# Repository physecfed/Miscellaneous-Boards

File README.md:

# Miscellaneous-Boards
A repository for miscellaneous KiCad and Altium PCB projects which don't fit cleanly into other repos. Primarily includes the *Level Shifter* series of boards, designed to perform logic level shifting between standard 3.3V LVCMOS signaling used by microcontrollers and industrial 0-10V signaling as used by PLCs, VFDs, and other such equipment. Mainly designed for interfacing to CNC equipment, and is designed for expedient production - hence the through-hole construction.

All boards in this repository are licensed under the CERN OHL v1.2 unless otherwise noted in a board-specific README file.

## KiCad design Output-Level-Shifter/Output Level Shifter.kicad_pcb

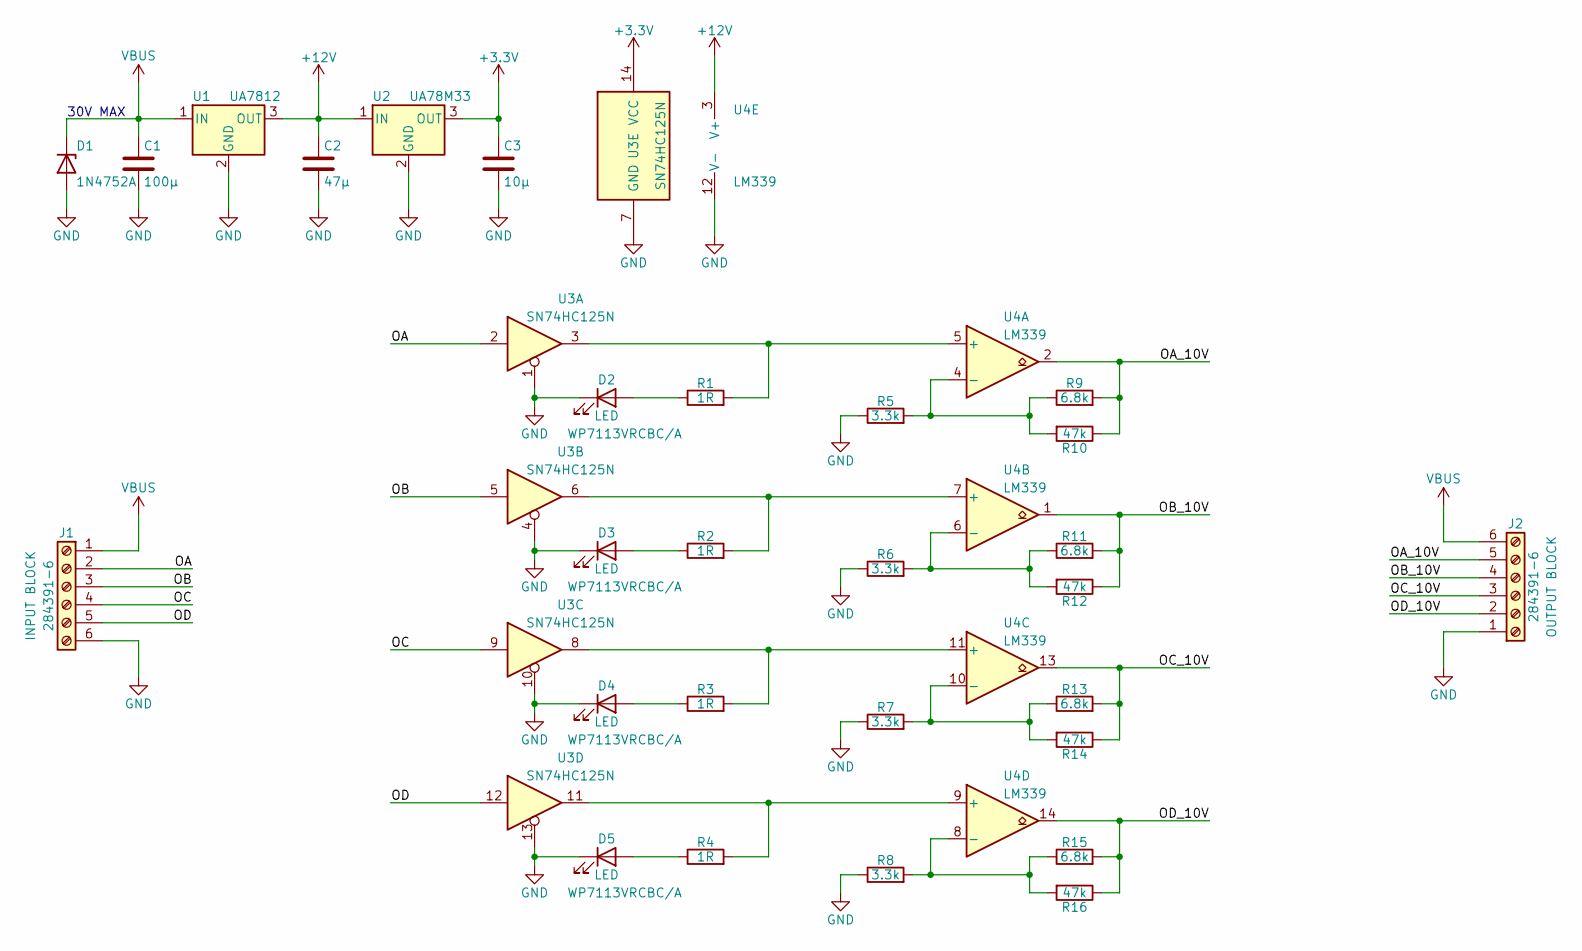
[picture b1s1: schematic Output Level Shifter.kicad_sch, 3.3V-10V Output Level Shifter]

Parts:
C1: 100µ; CP_Radial_D8.0mm_P5.00mm; Part MAL203690111E3
C2: 47µ; CP_Radial_D5.0mm_P2.00mm; Part ESK106M025AC3AA
C3: 10µ; CP_Radial_D5.0mm_P2.00mm; Part ESK106M025AC3AA
D1: 1N4752A; D_A-405_P7.62mm_Horizontal; Part 1N4751A
D2, D3, D4, D5: LED; LED_D5.0mm; Part WP7113VRCBC/A
J1: INPUT BLOCK; 284391-6; Part 284391-6
J2: OUTPUT BLOCK; 284391-6; Part 284391-6
R1, R2, R3, R4: 1R; R_Axial_DIN0207_L6.3mm_D2.5mm_P7.62mm_Horizontal; Part MF1/4DC1R00F
R5, R6, R7, R8: 3.3k; R_Axial_DIN0207_L6.3mm_D2.5mm_P7.62mm_Horizontal; Part MF1/4DCT52R3301F
R9, R11, R13, R15: 6.8k; R_Axial_DIN0207_L6.3mm_D2.5mm_P7.62mm_Horizontal; Part MF1/4DC6801F
R10, R12, R14, R16: 47k; R_Axial_DIN0207_L6.3mm_D2.5mm_P7.62mm_Horizontal; Part MF1/4DC4702F
U1: UA7812; TO-220-3_Horizontal_TabDown; Part UA7812CKCS
U2: UA78M33; TO-220-3_Horizontal_TabDown; Part UA78M33CKCS
U3: SN74HC125N; DIP-14_W7.62mm; Part SN74HC125N
U4: LM339; DIP-14_W7.62mm

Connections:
+3V3: C3.1, U2.3 (OUT), U3.14 (VCC)
+12V: C2.1, U1.3 (OUT), U2.1 (IN), U4.3 (V+)
/OA: J1.2, U3.2
/OA_10V: J2.5, R9.2, R10.1, U4.2
/OB: J1.3, U3.5
/OB_10V: J2.4, R11.2, R12.1, U4.1
/OC: J1.4, U3.9
/OC_10V: J2.3, R13.2, R14.1, U4.13
/OD: J1.5, U3.12
/OD_10V: J2.2, R15.2, R16.1, U4.14
GND: C1.2, C2.2, C3.2, D1.2 (A), D2.1 (K), D3.1 (K), D4.1 (K), D5.1 (K), J1.6, J2.1, R5.1, R6.1, R7.1, R8.1, U1.2 (GND), U2.2 (GND), U3.1, U3.4, U3.7 (GND), U3.10, U3.13, U4.12 (V-)
unnamed: D2.2 (A), R1.1
unnamed: D3.2 (A), R2.1
unnamed: D4.2 (A), R3.1
unnamed: D5.2 (A), R4.1
unnamed: R1.2, U3.3, U4.5 (+)
unnamed: R2.2, U3.6, U4.7 (+)
unnamed: R3.2, U3.8, U4.11 (+)
unnamed: R4.2, U3.11, U4.9 (+)
unnamed: R5.2, R9.1, R10.2, U4.4 (-)
unnamed: R6.2, R11.1, R12.2, U4.6 (-)
unnamed: R7.2, R13.1, R14.2, U4.10 (-)
unnamed: R8.2, R15.1, R16.2, U4.8 (-)
VBUS: C1.1, D1.1 (K), J1.1, J2.6, U1.1 (IN)

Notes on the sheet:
30V MAX

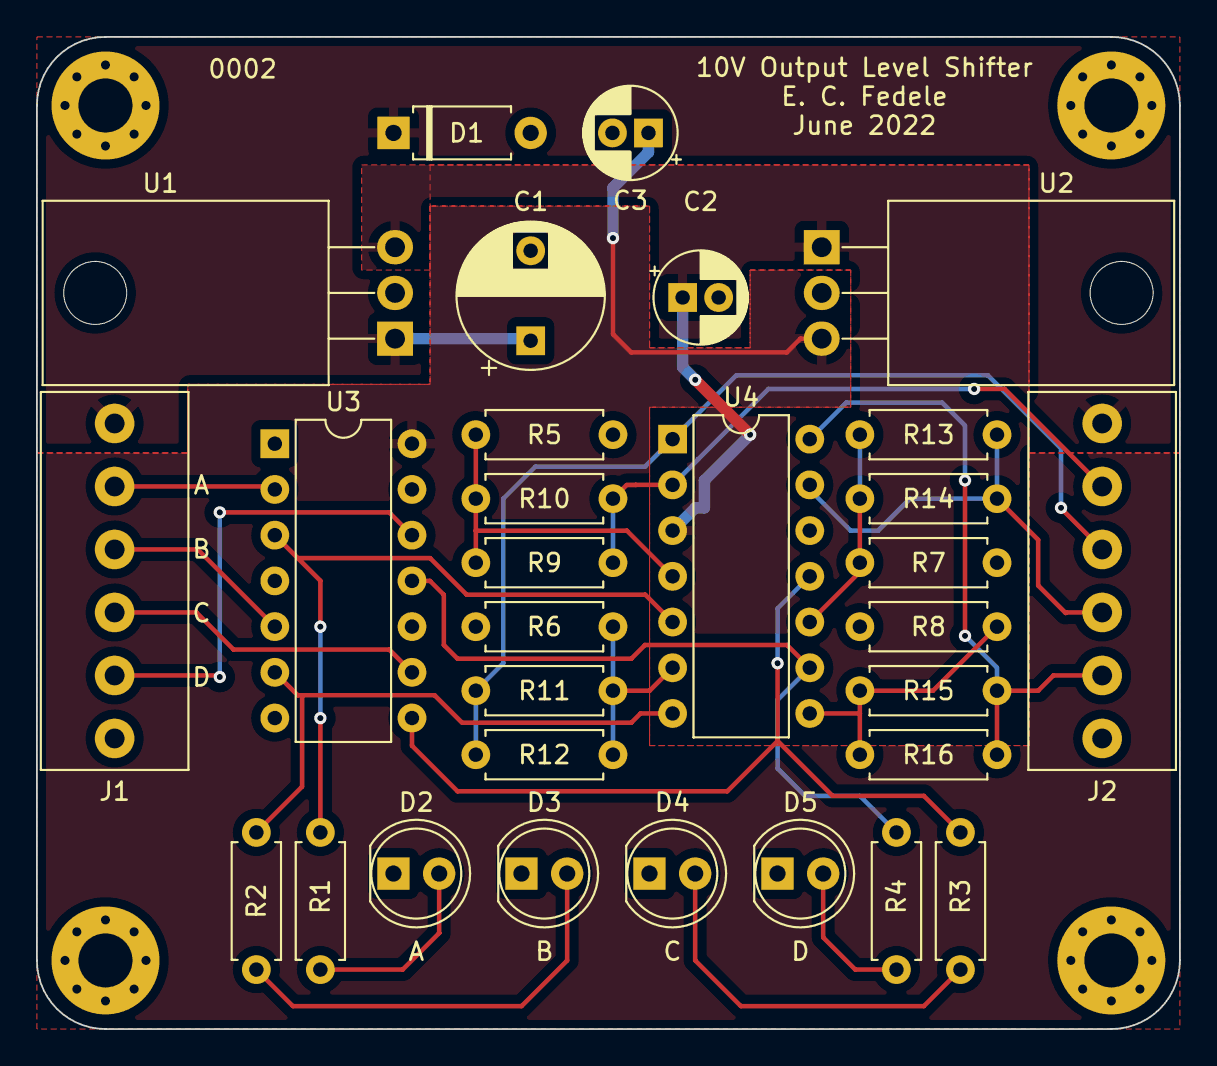
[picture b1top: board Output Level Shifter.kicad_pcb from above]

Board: 2 copper layers, 63.5 x 55.1 mm, 30 parts (0 on the bottom side), 24 nets.

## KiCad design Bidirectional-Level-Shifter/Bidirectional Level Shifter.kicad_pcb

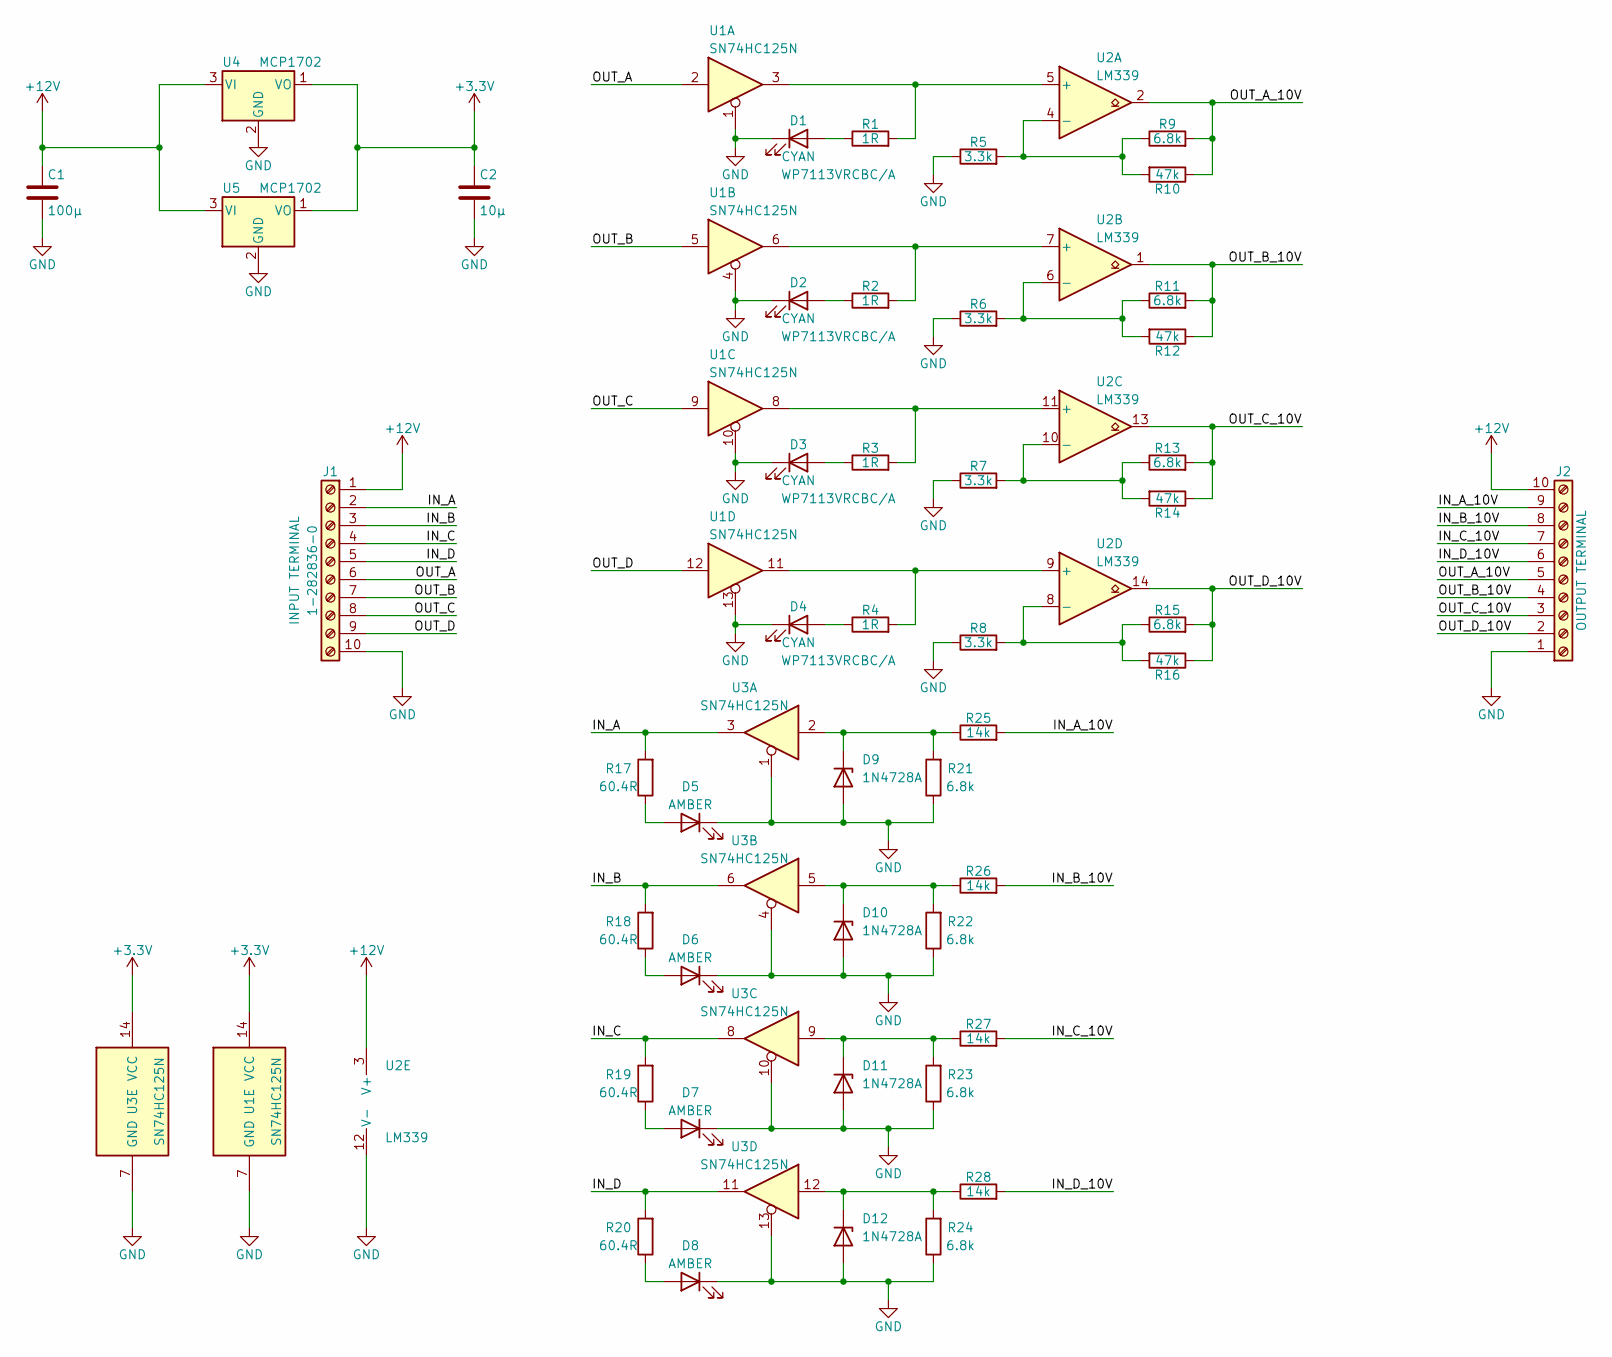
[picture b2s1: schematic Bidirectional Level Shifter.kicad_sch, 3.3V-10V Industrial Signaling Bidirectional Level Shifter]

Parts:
C1: 100μ; CP_Radial_D5.0mm_P2.00mm; Part ESK107M025AC3AA
C2: 10μ; CP_Radial_D5.0mm_P2.00mm; Part ESK106M025AC3AA
D1, D2, D3, D4: CYAN; LED_D5.0mm; Part WP7113VRCBC/A
D5, D6, D7, D8: AMBER; LED_D5.0mm; Part C503B-AAN-CY0B0251
D9, D10, D11, D12: 1N4728A; D_DO-41_SOD81_P7.62mm_Horizontal; Part 1N4728A
J1: INPUT TERMINAL; 1-282836-0; Part 1-282836-0
J2: OUTPUT TERMINAL; 1-282836-0
R1, R2, R3, R4: 1R; R_Axial_DIN0207_L6.3mm_D2.5mm_P7.62mm_Horizontal; Part MF1/4DC1R00F
R5, R6, R7, R8: 3.3k; R_Axial_DIN0207_L6.3mm_D2.5mm_P7.62mm_Horizontal; Part MF1/4DCT52R3301F
R9, R11, R13, R15, R21, R22, R23, R24: 6.8k; R_Axial_DIN0207_L6.3mm_D2.5mm_P7.62mm_Horizontal; Part MF1/4DC6801F
R10, R12, R14, R16: 47k; R_Axial_DIN0207_L6.3mm_D2.5mm_P7.62mm_Horizontal; Part MF1/4DC4702F
R17, R18, R19, R20: 60.4R; R_Axial_DIN0207_L6.3mm_D2.5mm_P7.62mm_Horizontal; Part MF1/4DC60R4F
R25, R26, R27, R28: 14k; R_Axial_DIN0207_L6.3mm_D2.5mm_P7.62mm_Horizontal; Part MF1/4CC1402F
U1, U3: SN74HC125N; DIP-14_W7.62mm; Part SN74HC125N
U2: LM339; DIP-14_W7.62mm; Part LM339AN/NOPB
U4, U5: MCP1702; TO-92_Inline; Part MCP1702-3302E/TO

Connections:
+3V3: C2.1, U1.14 (VCC), U3.14 (VCC), U4.1 (VO), U5.1 (VO)
+12V: C1.1, J1.1, J2.10, U2.3 (V+), U4.3 (VI), U5.3 (VI)
/IN_A: J1.2, R17.2, U3.3
/IN_A_10V: J2.9, R25.2
/IN_B: J1.3, R18.2, U3.6
/IN_B_10V: J2.8, R26.2
/IN_C: J1.4, R19.2, U3.8
/IN_C_10V: J2.7, R27.2
/IN_D: J1.5, R20.2, U3.11
/IN_D_10V: J2.6, R28.2
/OUT_A: J1.6, U1.2
/OUT_A_10V: J2.5, R9.2, R10.1, U2.2
/OUT_B: J1.7, U1.5
/OUT_B_10V: J2.4, R11.2, R12.1, U2.1
/OUT_C: J1.8, U1.9
/OUT_C_10V: J2.3, R13.2, R14.1, U2.13
/OUT_D: J1.9, U1.12
/OUT_D_10V: J2.2, R15.2, R16.1, U2.14
GND: C1.2, C2.2, D1.1 (K), D2.1 (K), D3.1 (K), D4.1 (K), D5.1 (K), D6.1 (K), D7.1 (K), D8.1 (K), D9.2 (A), D10.2 (A), D11.2 (A), D12.2 (A), J1.10, J2.1, R5.1, R6.1, R7.1, R8.1, R21.1, R22.1, R23.1, R24.1, U1.1, U1.4, U1.7 (GND), U1.10, U1.13, U2.12 (V-), U3.1, U3.4, U3.7 (GND), U3.10, U3.13, U4.2 (GND), U5.2 (GND)
unnamed: D1.2 (A), R1.1
unnamed: D2.2 (A), R2.1
unnamed: D3.2 (A), R3.1
unnamed: D4.2 (A), R4.1
unnamed: D5.2 (A), R17.1
unnamed: D6.2 (A), R18.1
unnamed: D7.2 (A), R19.1
unnamed: D8.2 (A), R20.1
unnamed: R1.2, U1.3, U2.5 (+)
unnamed: R2.2, U1.6, U2.7 (+)
unnamed: R3.2, U1.8, U2.11 (+)
unnamed: R4.2, U1.11, U2.9 (+)
unnamed: R5.2, R9.1, R10.2, U2.4 (-)
unnamed: R6.2, R11.1, R12.2, U2.6 (-)
unnamed: R8.2, R15.1, R16.2, U2.8 (-)
unnamed: R7.2, R13.1, R14.2, U2.10 (-)
unnamed: D9.1 (K), R21.2, R25.1, U3.2
unnamed: D10.1 (K), R22.2, R26.1, U3.5
unnamed: D11.1 (K), R23.2, R27.1, U3.9
unnamed: D12.1 (K), R24.2, R28.1, U3.12

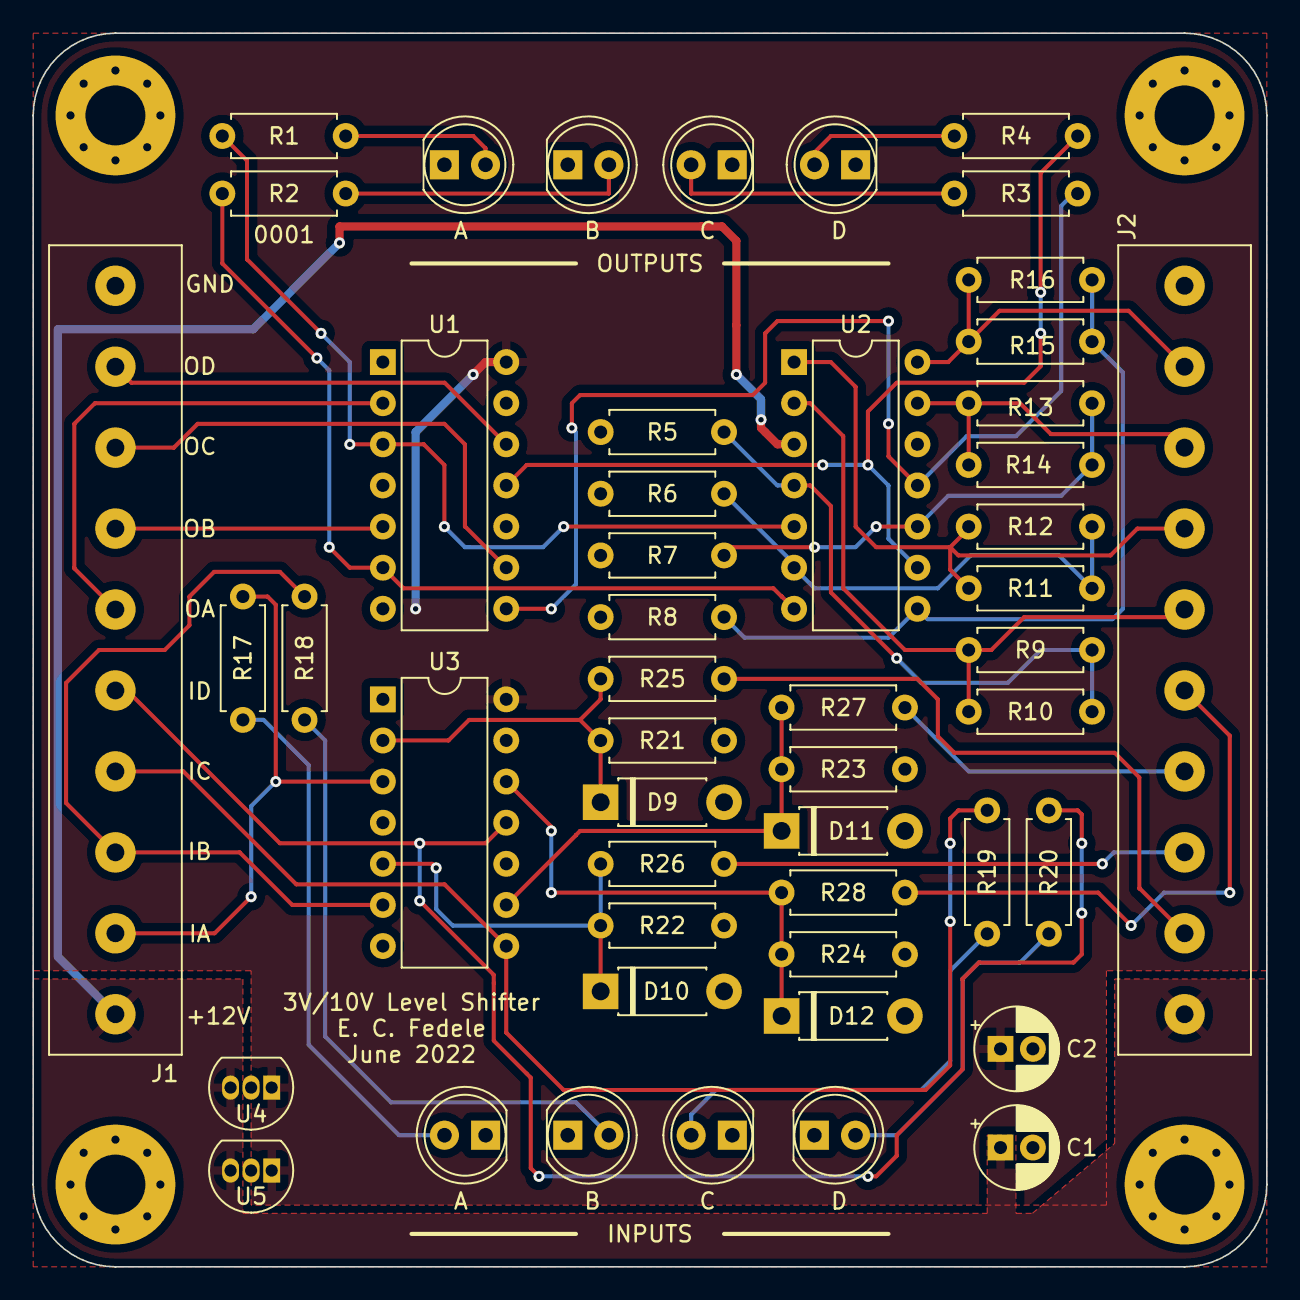
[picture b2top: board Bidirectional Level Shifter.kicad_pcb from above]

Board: 2 copper layers, 76.2 x 76.2 mm, 49 parts (0 on the bottom side), 39 nets.

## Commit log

2022-07-05 Added bidirectional 3-10V level shifter
2022-07-07 Added Output Level Shifter
2022-07-07 Added CERN OHL v1.2 license text manually
